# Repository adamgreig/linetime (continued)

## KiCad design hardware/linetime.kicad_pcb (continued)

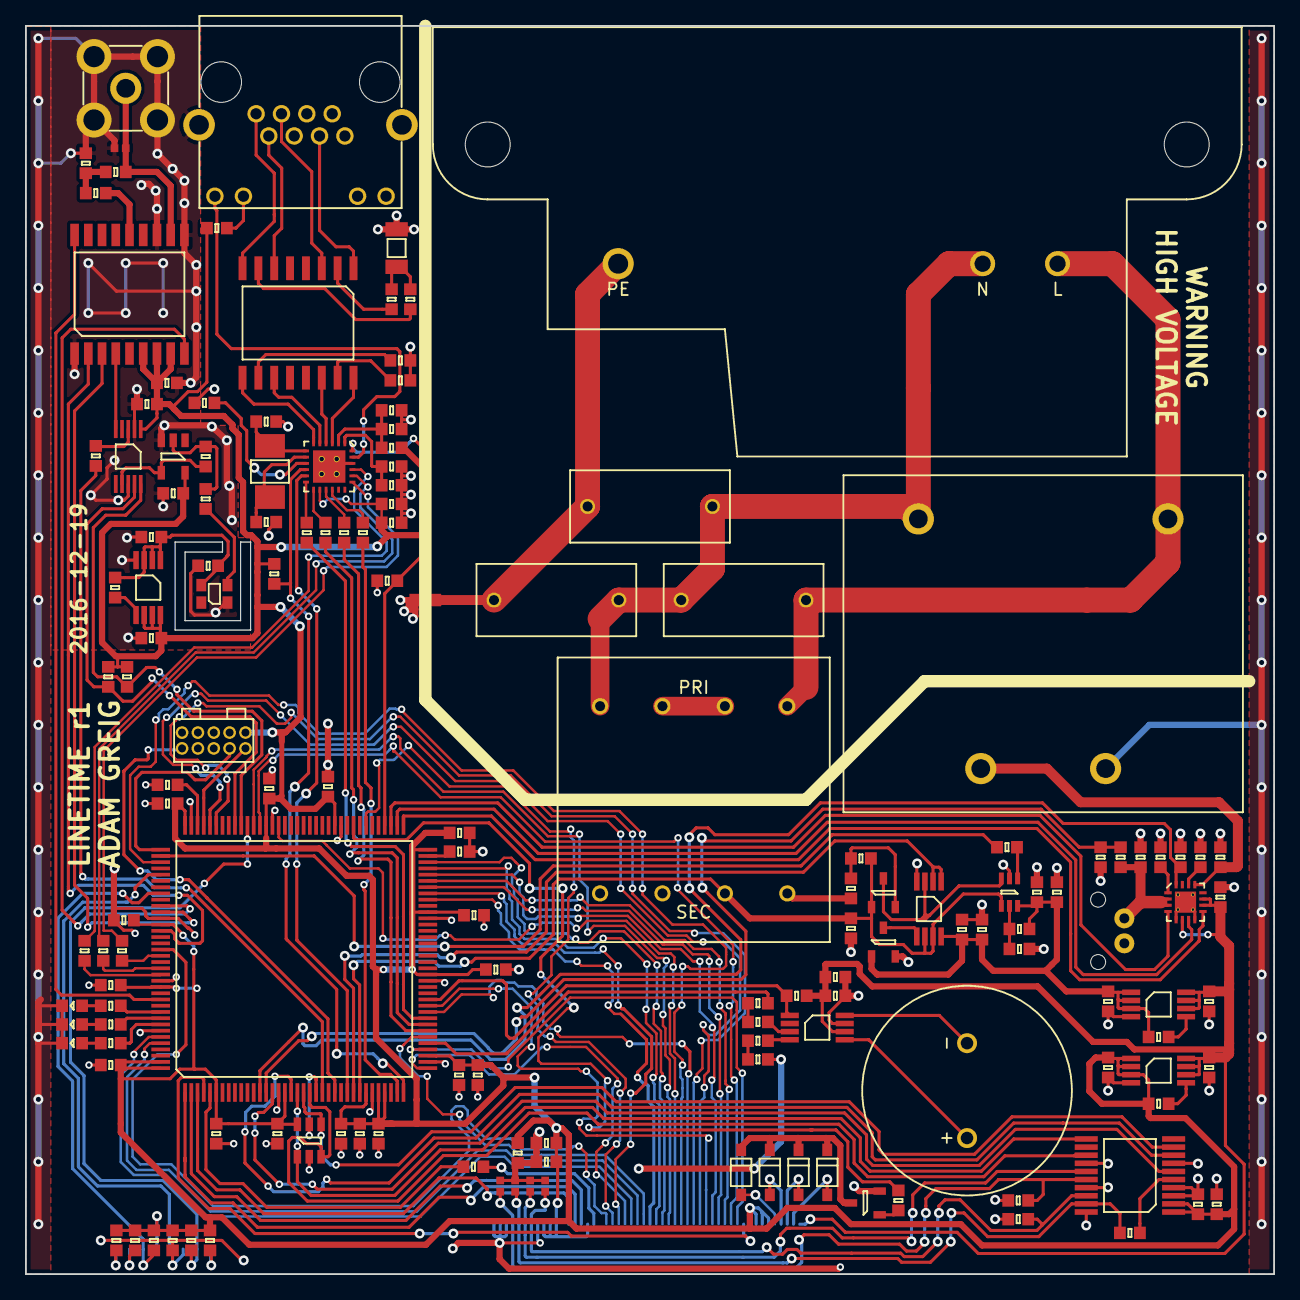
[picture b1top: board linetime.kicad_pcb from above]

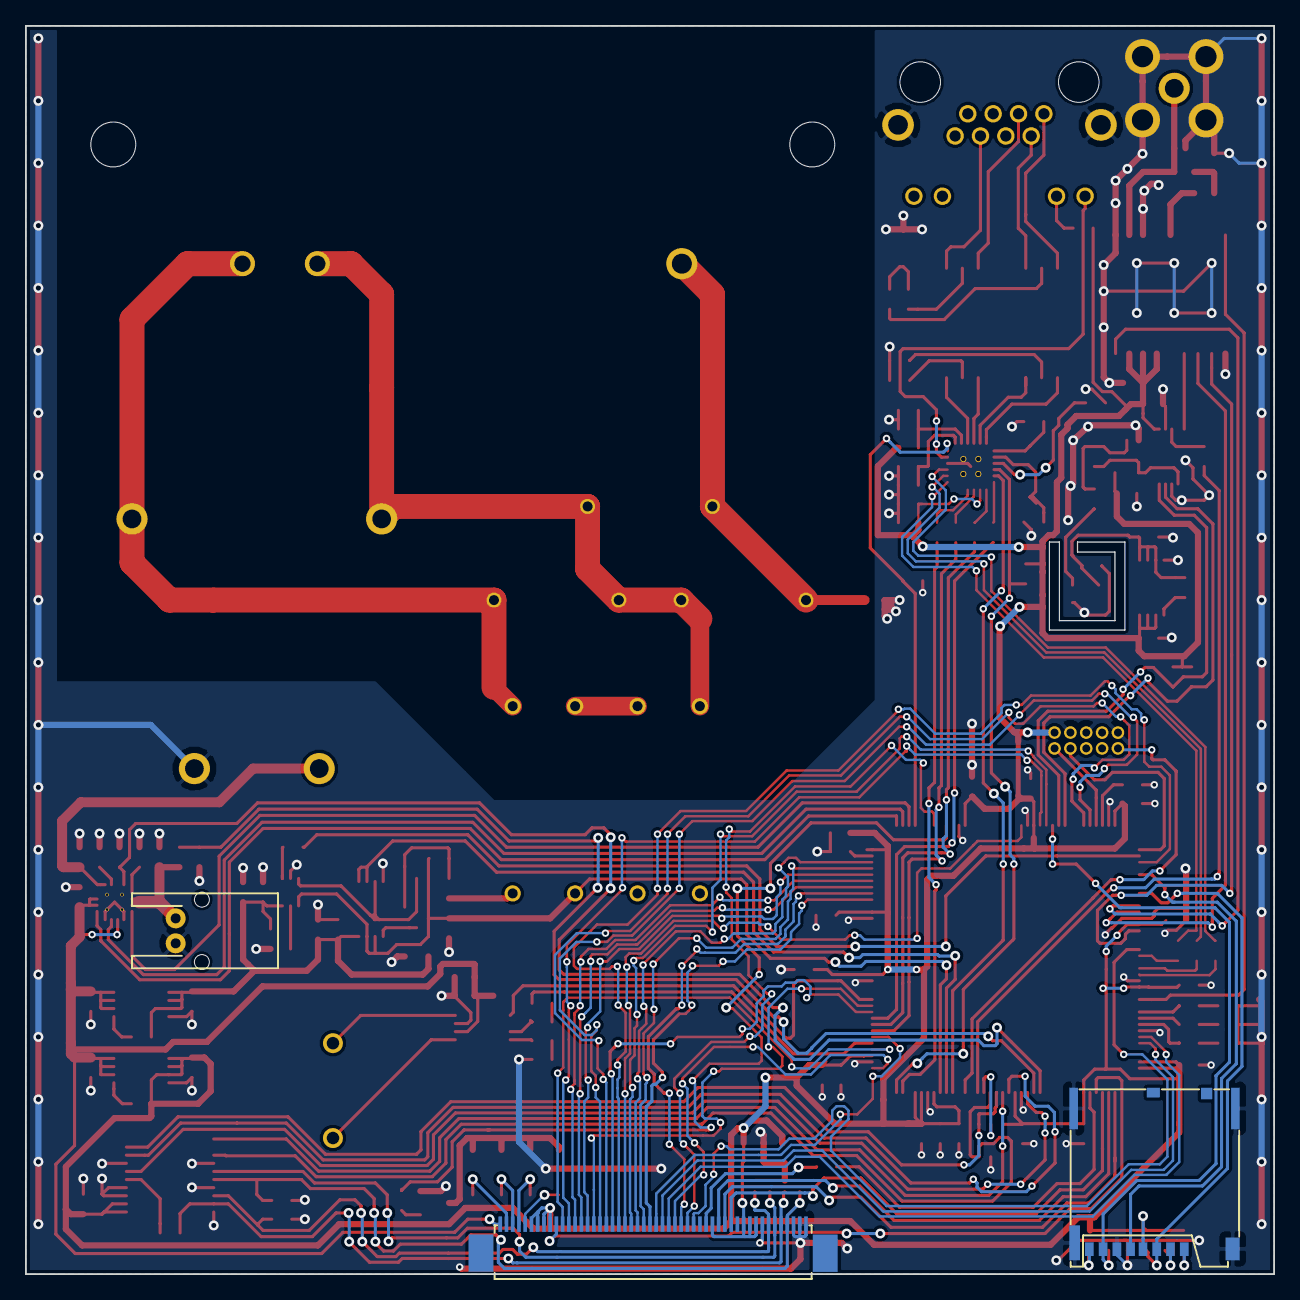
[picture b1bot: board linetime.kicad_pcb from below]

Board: 2 copper layers, 100.0 x 100.0 mm, 154 parts (3 on the bottom side), 153 nets.

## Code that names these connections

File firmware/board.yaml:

name: Linetime
lsefreq: 0
hsefreq: 26000000
voltage: 3.3
mcutype: STM32F767xx
default: input, pushpull, starthigh, pullup, highspeed
pins:
  # SWD
  SWDIO: pa13, af0, pulldown
  SWCLK: pa14, af0, pulldown

  # Ethernet RMII
  RMII_MDIO: pa2, af11
  RMII_MDC: pc1, af11
  RMII_REF_CLK: pa1, af11
  RMII_CRS_DV: pa7, af11
  RMII_RXD0: pc4, af11
  RMII_RXD1: pc5, af11
  RMII_TX_EN: pg11, af11
  RMII_TXD0: pg13, af11
  RMII_TXD1: pg14, af11
  PHY_RST: pb15, output, floating, startlow

  # LCD on TFT-LCD controller and on SPI4, backlight PWM on TIM4 ch1
  LCD_VSYNC: pa4, af14
  LCD_HSYNC: pc6, af14
  LCD_DOTCLK: pe14, af14
  LCD_DE: pe13, af14
  LCD_R7: pe15, af14
  LCD_R6: pb1, af9
  LCD_R5: pa12, af14
  LCD_R4: pa11, af14
  LCD_R3: pb0, af9
  LCD_R2: pc10, af14
  LCD_G7: pg8, af14
  LCD_G6: pc7, af14
  LCD_G5: pb11, af14
  LCD_G4: pb10, af14
  LCD_G3: pe11, af14
  LCD_G2: pa6, af14
  LCD_B7: pb9, af14
  LCD_B6: pb8, af14
  LCD_B5: pa3, af14
  LCD_B4: pe12, af14
  LCD_B3: pd10, af14
  LCD_B2: pg10, af14
  LCD_RST: pe5, output
  LCD_DCX: pe3, output
  LCD_SDA: pe6, af5
  LCD_SCL: pe2, af5
  LCD_CS: pe4, output
  LCD_BACKLIGHT: pd12, af2, floating

  # Touchscreen controller (also ROM SPI bus) on SPI5
  TOUCH_INT: pf5
  TOUCH_CS: pf6, output
  TOUCH_SCK: pf7, af5
  TOUCH_SDO: pf8, af5
  TOUCH_SDI: pf9, af5
  EEPROM_CS: pf10, output

  # Sounder
  SOUNDER: pa5, analog
  SOUNDER_SD: pb2, output, startlow

  # Battery management on ADC3
  BATT_I_CHG: pf3, floating, analog
  BATT_V_MON: pf4, floating, analog
  BATT_CHG: pb12
  BATT_PGOOD: pb13
  BATT_CE: pb14, output

  # GPS (PPS on TIM2 ch2)
  GPS_RXD: pd5, af7
  GPS_TXD: pd6, af7
  GPS_RESET: pd4, output
  GPS_PPS: pb3, floating, af1

  # CS2100 PLL on I2C3
  CS2100_SCL: pa8, af4
  CS2100_SDA: pc9, af4
  CS2100_CLK: ph0, floating

  # Mains on ADC1 and ADC2 and TIM2 ch1
  MAINS_BIAS: pc3, floating, analog
  MAINS_WAVE: pc2, floating, analog
  MAINS_ZC: pa15, floating, af1

  # LEDs
  LED_RED: pb5, output, startlow
  LED_YLW: pb6, output, startlow
  LED_GRN: pb7, output, startlow

  # MicroSD card
  USD_CMD: pd2, af12
  USD_CLK: pc12, af12
  USD_DAT0: pc8, af12

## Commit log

2016-11-24 Initial commit.
2016-12-10 WIP. Saving ethernet sheet before I take out PoE.
2016-12-14 schematic basically done...
2016-12-16 WIP routing
2016-12-18 22 airwires to go
2016-12-18 17 airwires
2016-12-18 4 to go!!
2016-12-18 565RGB and 2 airwires left yay
2016-12-19 cleaned up all the fast lines
2016-12-19 goodness. routed all airwires.
2016-12-19 tidying
2016-12-19 gerbers to manufacturing. gulp.
2016-12-21 add farnell part numbers for passives
2016-12-23 start firmware
2016-12-24 untested gps driver
2016-12-24 add untested cs2100 config and clock swapping stuff
2016-12-24 update todo
2016-12-25 make a start on mains monitoring bits
2016-12-25 futher work on processing mains-related events
2016-12-25 update todo. merry christmas, btw
2016-12-27 further work on rms/frequency/UTC calcs
2016-12-27 grab waveform at half/full adc dma interrupts and subsample
2016-12-29 add stickerbom
2016-12-30 add some notes on r1 hardware
2016-12-30 tweak ublox, cs2100, etc, etc, to get board up and running
2016-12-30 start logging to sd card, kinda
2016-12-30 fix more timer issues
2016-12-30 hmm maybe basically logging-to-sd working
2016-12-30 ok... deployed...
2017-01-02 add prototype view/count script
2017-01-02 update to 100MHz timer
2017-01-03 refactor measurements. much better.
2017-01-05 omg, caches, dacs, dmas
2017-01-05 bounce bounce bounce
2017-01-06 reduce draw window size to prevent weird issue
2017-01-06 don't need no stinkin' ugfx anyway
2017-01-07 draw a clock and beep and stuff
2017-01-08 ugh... gui, lcd, network, packet loss, etc
2017-01-13 add homebrew ethernet lol
2017-01-13 improve diy eth
2017-01-15 diyeth mostly done? see msg
    so.. everything is awful
    *) need to __DMB() while interacting with the eth descriptors when in SRAM1/2
    or weird things happen, as well as needing cache off/disabled by MPU/managed
    *) once you do __DMB() you can use SRAM1/2 without issue, just as good as DTCM
    *) however still terrible packet loss on linetime
    *) packet loss is always due to bad FSC due to RXD0 bit flips
2017-01-22 fix chibios mac mem sync
2017-03-29 add case drawing stuff
2017-04-25 wait for pll off before swapping pll source
2017-05-08 mandelbrot thing
2017-05-08 fix up lcd clock
2017-05-08 fix cache cleaning in diyeth
2020-05-29 Try using EG
